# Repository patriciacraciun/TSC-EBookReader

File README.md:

# README 

## Descriere Generala

Acest proiect reprezinta un sistem integrat cu afisaj E-Paper, conectivitate wireless si mai multi senzori. Totul este construit in jurul microcontrollerului ESP32-C6, care ofera suport pentru WiFi 6 si Bluetooth LE.
Proiectul include atat partea de incarcare si monitorizare a bateriei, cat si stocare externa si masurare a conditiilor de mediu.

---

## Etapele de Implementare

- Am inceput cu realizarea schemei electrice, conectand toate componentele relevante la ESP32-C6.
- Apoi am trecut la layout-ul PCB-ului in 2D, unde am rutat liniile de date si alimentare.
- Am creat planuri de masa (GND plane) atat pe stratul superior, cat si inferior.
- Am folosit reguli custom pentru latimea traseelor de alimentare si distantele minime fata de alte semnale.
- Conectorii au fost pozitionati astfel incat sa fie usor accesibili (ex: Qwiic pentru senzori externi).
- Am adaugat pad-uri de test (TP) pentru debugging mai usor dupa asamblare.
- Am generat modele 3D pentru a verifica compatibilitatea mecanica si pozitionarea componentelor in carcasa.
---

## Diagrama Bloc

```text
         +------------+
         |  Baterie   |
         +------------+
               |
               v
       +----------------+
       |  Charging IC   |<-- USB-C
       +----------------+
               |
               v
       +----------------+
       |      LDO       | --> 3.3V
       +----------------+
               |
      +--------+--------+--------+--------+--------+
      v        v        v        v        v
   +------+ +--------+ +------+ +------+ +--------+
   | ESP  | |Display | | RTC  | | BME  | | Butoane|
   | -C6  | |(SPI)   | |(I2C) | |(I2C) | |(GPIO)  |
   +------+ +--------+ +------+ +------+ +--------+
               |
               v
           +---------+
           | Flash   |
           |  NOR    |
           | (SPI)   |
           +---------+
               |
               v
           +---------+
           | SD Card |
           |  (SPI)  |
           +---------+
```

---

## BOM (Bill Of Materials)

| Componenta                        | Link Cumparare                                                                                                   | Datasheet                                                                                          
|-----------------------------------|------------------------------------------------------------------------------------------------------------------|---------------------------------------------------------------------------------------------------
| 112A-TAAR-R03 ATTEND              | https://store.comet.srl.ro/Catalogue/Product/43497/                                                              | https://www.snapeda.com/parts/112A-TAAR-R03/Attend/datasheet/                                    
| BD5229G-TR                        | https://www.digikey.com/en/products/detail/rohm-semiconductor/BD5229G-TR/3663792                                 | https://fscdn.rohm.com/en/products/databook/datasheet/ic/power/voltage_detector/bd52xxg-e.pdf    
| ESP32 WROVER BME680 Sensor        | https://store.comet.srl.ro/Catalogue/Product/50164/                                                              | https://www.bosch-sensortec.com/media/boschsensortec/downloads/datasheets/bst-bme680-ds001.pdf   
| LED CHG_LED                       | https://ro.mouser.com/ProductDetail/Kingbright/KP-1608SURCK?qs=2JU0tDl2GZ3FuyEWfBV1%2Fg==                        | https://www.snapeda.com/parts/KP-1608SURCK/Kingbright/datasheet/                                 
| Condensator C0402                 | https://ro.mouser.com/c/passive-components/capacitors/ceramic-capacitors/?q=CC0402                               | https://componentsearchengine.com/Datasheets/2/CC0402MRX5R5BB106.pdf                             
| Condensator Tant                  | https://ro.mouser.com/ProductDetail/KYOCERA-AVX/TAJW107M010RNJ?qs=Wtp%252Bf%2FAeVqIH8v1VxV%252B1Rg%3D%3D         | https://ro.mouser.com/datasheet/2/40/TAJ-3165264.pdf                                             
| Q1 DMG2305UX-7                    | https://www.digikey.com/en/products/detail/diodes-incorporated/DMG2305UX-7/4340666                               | https://www.diodes.com/assets/Datasheets/DMG2305UX.pdf                                           
| RTC MODULE DS3231SN#              | https://www.snapeda.com/parts/DS3231SN%23/Analog+Devices/view-part/?ref=eda                                      | https://www.snapeda.com/parts/DS3231SN%23/Analog%20Devices/datasheet/                            
| ESP32 C6 WROOM-1-N8               | https://ro.mouser.com/ProductDetail/Espressif-Systems/ESP32-C6-WROOM-1-N8?qs=8Wlm6%252BaMh8ST02Gmwp74cw%3D%3D    | https://www.snapeda.com/parts/ESP32-C6-WROOM-1-N8/Espressif%20Systems/datasheet/                 
| FH34SRJ-24S-0.5SH(99)             | https://ro.mouser.com/ProductDetail/Hirose-Connector/FH34SRJ-24S-0.5SH99?qs=vcbW%252B4%252BSTIpKBl5ap9J8Fw%3D%3D | https://www.snapeda.com/parts/FH34SRJ-24S-0.5SH(99)/Hirose%20Connector/datasheet/                
| MAX 17048G+T10                    | https://www.snapeda.com/parts/MAX17048G+T10/Analog+Devices/view-part/?ref=eda                                    | https://www.snapeda.com/parts/MAX17048G+T10/Analog%20Devices/datasheet/                          
| MBR0530 Schottky Diode            | https://www.snapeda.com/parts/MBR0530/Onsemi/view-part/?ref=snap                                                 | https://www.snapeda.com/parts/MBR0530/ON%20Semiconductor/datasheet/                              
| MCP73831 Power Management         | https://www.snapeda.com/parts/MCP73831T-2ACI/OT/Microchip/datasheet/                                             | https://www.snapeda.com/parts/MCP73831T-2ACI/OT/Microchip/datasheet/                             
| PFMF.050.1                        | https://ro.mouser.com/ProductDetail/EPCOS-TDK/B72520T0350K062?qs=dEfas%2FXlABIszF52uu7vrg%3D%3D                  | https://www.tdk-electronics.tdk.com/inf/75/db/CTVS_14/Surge_protection_series.pdf                
| PGB1010603MR                      | https://www.snapeda.com/parts/PGB1010603MR/Littelfuse/view-part/?ref=eda                                         | https://www.snapeda.com/parts/PGB1010603MR/Littelfuse%20Inc./datasheet/                          
| QWIIC_RIGHT_ANGLE CONNECTOR       | https://ro.mouser.com/ProductDetail/SparkFun/PRT-14417?qs=wd5RIQLrsJhgdz%2FpmZ%2F3GQ==                           | https://ro.mouser.com/datasheet/2/813/Qwiic_Connector_Datasheet-1223982.pdf                      
| Rezistenta R0402                  | https://grabcad.com/library/resistor-0402-1)                                                                     | https://www.yageo.com/upload/media/product/products/datasheet/rchip/PYu-RC_Group_51_RoHS_L_12.pdf
| SD0805S020S1R0                    | https://ro.mouser.com/ProductDetail/KYOCERA-AVX/SD0805S020S1R0?qs=jCA%252BPfw4LHbpkAoSnwrdjw%3D%3D               | https://ro.mouser.com/datasheet/2/40/schottky-3165252.pdf                                        
| Si1308EDL-T1-GE3 MOSFET           | https://www.snapeda.com/parts/SI1308EDL-T1-GE3/Vishay+Siliconix/view-part/?welcome=home&ref=eda                  | https://www.snapeda.com/parts/SI1308EDL-T1-GE3/Vishay%20Siliconix/datasheet/                     
| USB4110-GF-A                      | https://ro.mouser.com/ProductDetail/GCT/USB4110-GF-A?qs=KUoIvG%2F9IlYiZvIXQjyJeA%3D%3D                           | https://ro.mouser.com/datasheet/2/837/GCT_USB4110_Product_Drawing___20k_cycles-3455479.pdf       
| USBLC6-2SC6Y                      | https://ro.mouser.com/ProductDetail/STMicroelectronics/USBLC6-2SC6Y?qs=gNDSiZmRJS%2FOgDexvXkdow%3D%3D            | https://ro.mouser.com/datasheet/2/389/usblc6_2sc6y-1852505.pdf                                   
| W25Q512JVEIQ                      | https://www.snapeda.com/parts/W25Q512JVEIQ/Winbond+Electronics/view-part/?ref=eda)                               | https://www.winbond.com/resource-files/W25Q512JV%20SPI%20RevB%2006252019%20KMS.pdf               
| XC6220A331MR-G                    | https://componentsearchengine.com/part-view/XC6220A331MR-G/Torex                                                 | https://product.torexsemi.com/system/files/series/xc6220.pdf                                     
| 744043680 BOBINA                  | https://ro.mouser.com/ProductDetail/Wurth-Elektronik/744043680?qs=PGXP4M47uW6VkZq%252BkzjrHA%3D%3D               | https://www.we-online.com/components/products/datasheet/744043680.pdf                            

---

## Functionalitate Hardware

Microcontrollerul ESP32-C6 gestioneaza toate functiile sistemului:

- **Display E-Paper**: conectat prin SPI. Este utilizat pentru afisajul principal.
- **BME688**: senzor de temperatura, umiditate, presiune si VOC, conectat prin I2C.
- **RTC DS3231**: modul de timp real, pentru pastrarea orei chiar si cand dispozitivul este oprit.
- **SD Card**: stocare externa, comunicare SPI.
- **Memorie NOR Flash**: pentru date si firmware, interfata SPI.
- **Charging controller (MCP73831)**: incarca bateria Li-Po prin USB-C.
- **Fuel gauge (MAX17048)**: monitorizeaza nivelul de incarcare al bateriei.
- **Qwiic Connector**: pentru senzori modulari, I2C.
- **Buton BOOT si RESET**: conectate la GPIO pentru programare si control.

---

## Alocarea Pinilor ESP32-C6

| Componenta                | Interfata | Pini ESP32-C6        | Observatii                          |
|--------------------------|-----------|----------------------|--------------------------------------|
| Display E-Paper          | SPI       | IO7, IO6, IO10, IO5, IO23, IO3 | MOSI, SCK, CS, DC, RST, BUSY       |
| BME688 + RTC             | I2C       | IO21 (SDA), IO22 (SCL) | Bus comun cu pull-up                |
| MAX17048 Battery Gauge   | I2C       | IO19 (SCL), IO20 (SDA)| Separat pentru alimentare baterie   |
| SD Card                  | SPI       | IO4 (CS) + MOSI/SCK/MISO| Partajate cu Flash/Display         |
| Flash NOR                | SPI       | IO12 (CS)             | Pe acelasi bus SPI                  |
| USB                      | USB       | IO13 (D+), IO12 (D-)  | Conexiune directa la USB-C          |
| Buton Reset              | GPIO      | EN                    | Reset hardware                      |
| Buton Boot               | GPIO      | IO9                   | Intrare manuala in modul bootloader |

---

## Alte Observatii

- Placa are pad-uri de test (TP) pentru debugging usor.
- Conectorul Qwiic permite extinderea cu alti senzori.
- Diodele ESD protejeaza liniile sensibile (USB, SPI, alimentare).
- Planurile de masa au fost implementate pe ambele straturi pentru stabilitate si protectie EMI.
- Rutarea a fost facuta manual, tinand cont de distantele minime si traseele de putere.
- PCB-ul este compact si poate fi reprodus usor in mai multe exemplare.
- Designul este compatibil cu carcase printate 3D.

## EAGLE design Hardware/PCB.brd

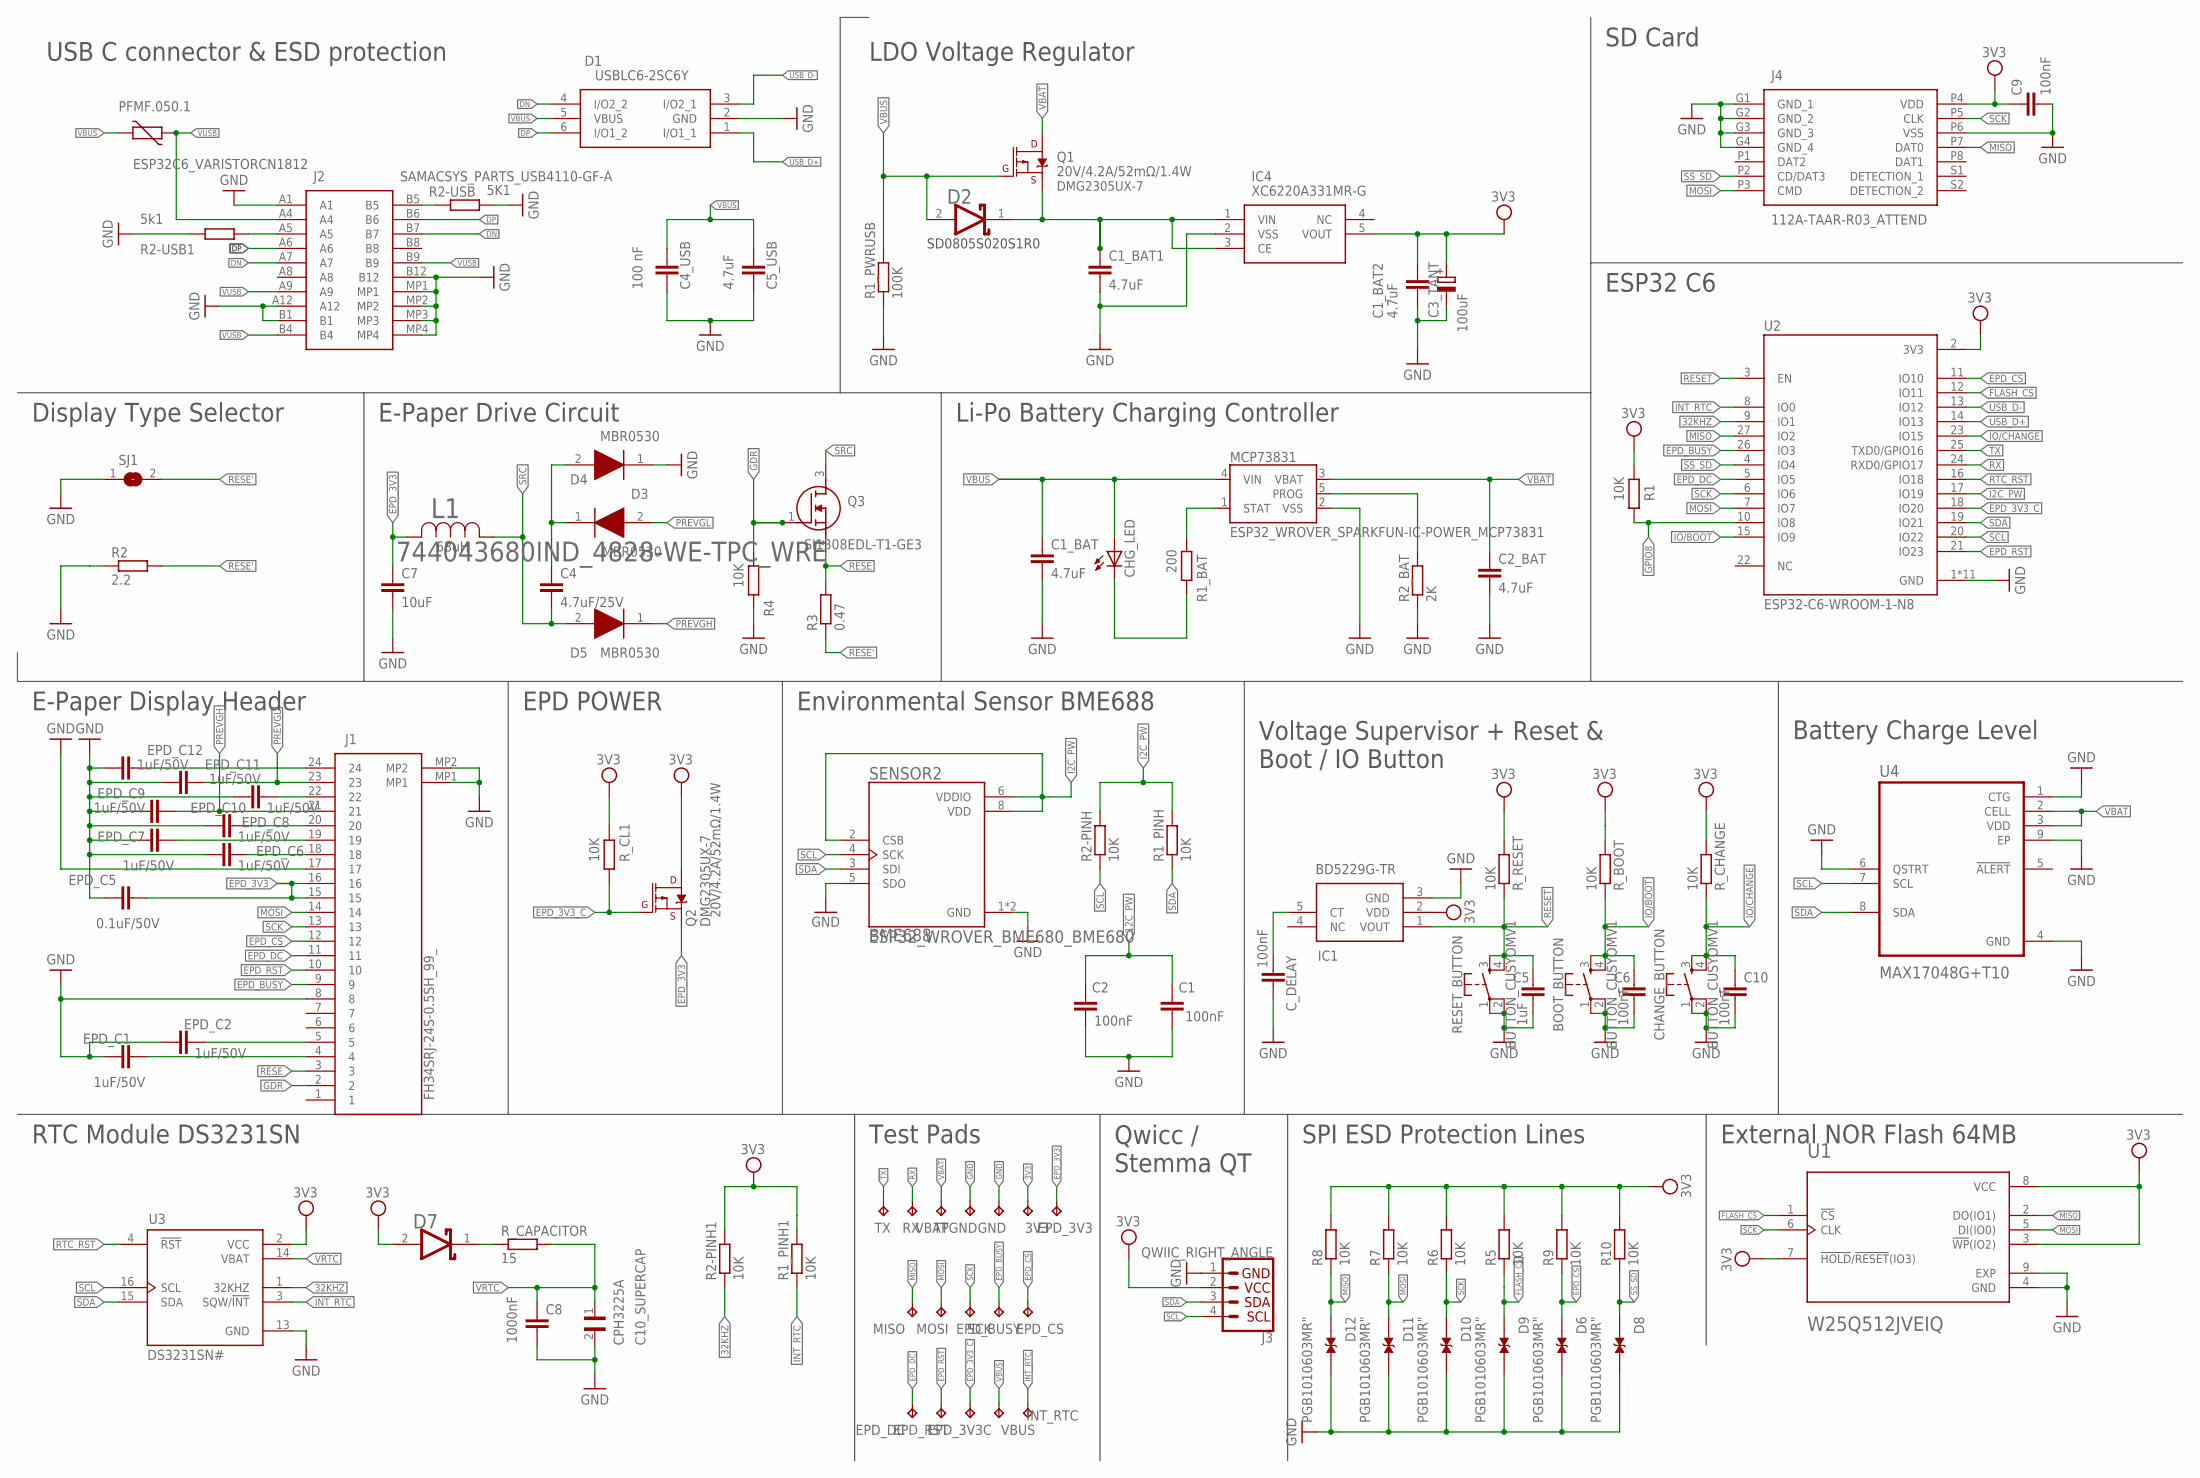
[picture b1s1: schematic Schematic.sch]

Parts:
3V3: TPTP20R; TP20R
BOOT_BUTTON: BUTTON_CUSYOMV1; MYBUTTON
C1, C2: 100nF; ESP32_WROVER_EAGLE-LTSPICE_C0402
C1_BAT, C1_BAT1, C1_BAT2, C2_BAT: 4.7uF; EAGLE-LTSPICE_C0402
C3_TANT: 100uF; RCL_CT3528
C4: 4.7uF/25V; EAGLE-LTSPICE_C0402
C4_USB: 100 nF; ESP32_WROVER_EAGLE-LTSPICE_C0402
C5: 1uF; EAGLE-LTSPICE_C0402
C5_USB: 4.7uF; ESP32_WROVER_EAGLE-LTSPICE_C0402
C6, C9, C10: 100nF; EAGLE-LTSPICE_C0402
C7: 10uF; EAGLE-LTSPICE_C0402
C8: 1000nF; EAGLE-LTSPICE_C0402
C10_SUPERCAP: CPH3225A; CAPCP3225X100N
CHANGE_BUTTON: BUTTON_CUSYOMV1; MYBUTTON
CHG_LED: ADAFRUIT_LEDCHIP-LED0603; ADAFRUIT_CHIP-LED0603
C_DELAY: 100nF; EAGLE-LTSPICE_C0402
D1: USBLC6-2SC6Y; SOT95P280X145-6N
D2, D7: ESP32_WROVER_AVX---SD0805S020S1R0_AVX_SD0805S020S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; ESP32_WROVER_AVX---SD0805S020S1R0_AVX_SD0805S020S1R0_0
D3, D4, D5: MBR0530; SOD3716X135N
D6, D8, D9, D10, D11, D12: PGB1010603MR"; DIOC1608X36N
EPD_3V3, EPD_3V3C: TPTP20R; TP20R
EPD_BUSY: TPTP20R; TP20R
EPD_C1, EPD_C2, EPD_C6, EPD_C7, EPD_C8, EPD_C9, EPD_C10, EPD_C11, EPD_C12: 1uF/50V; EAGLE-LTSPICE_C0402
EPD_C5: 0.1uF/50V; EAGLE-LTSPICE_C0402
EPD_CS: TPTP20R; TP20R
EPD_DC: TPTP20R; TP20R
EPD_RST: TPTP20R; TP20R
GND: TPTP20R; TP20R
IC1: BD5229G-TR; SOT95P280X125-5N
IC4: XC6220A331MR-G; SOT95P280X120-5N
INT_RTC: TPTP20R; TP20R
J1: FH34SRJ-24S-0.5SH_99_; FH34SRJ24S05SH99
J2: SAMACSYS_PARTS_USB4110-GF-A; SAMACSYS_PARTS_USB4110GFA
J3: QWIIC_RIGHT_ANGLE; JST04_1MM_RA
J4: 112A-TAAR-R03_ATTEND; 112ATAARR03ATTEND
L1: 744043680IND_4828-WE-TPC_WRE; IND_4828-WE-TPC_WRE
MCP73831: ESP32_WROVER_SPARKFUN-IC-POWER_MCP73831; ESP32_WROVER_SPARKFUN-IC-POWER_SOT23-5
MISO: TPTP20R; TP20R
MOSI: TPTP20R; TP20R
PFMF.050.1: ESP32C6_VARISTORCN1812; ESP32C6_VARISTOR_CT/CN1812
Q1, Q2: 20V/4.2A/52mΩ/1.4W; ESP32_WROVER_SPARKFUN-DISCRETESEMI_SOT23-3
Q3: SI1308EDL-T1-GE3; SOT65P210X110-3N
R1, R1_PINH, R1_PINH1, R2-PINH, R2-PINH1, R4, R5, R6, R7, R8, R9, R10: 10K; ESP32_WROVER_EAGLE-LTSPICE_R0402
R1_BAT: 200; ESP32_WROVER_EAGLE-LTSPICE_R0402
R1_PWRUSB: 100K; ESP32_WROVER_EAGLE-LTSPICE_R0402
R2: 2.2; ESP32_WROVER_EAGLE-LTSPICE_R0402
R2-USB: 5K1; ESP32_WROVER_EAGLE-LTSPICE_R0402
R2-USB1: 5k1; ESP32_WROVER_EAGLE-LTSPICE_R0402
R2_BAT: 2K; ESP32_WROVER_EAGLE-LTSPICE_R0402
R3: 0.47; ESP32_WROVER_EAGLE-LTSPICE_R0402
RESET_BUTTON: BUTTON_CUSYOMV1; MYBUTTON
RX: TPTP20R; TP20R
R_BOOT: 10K; ESP32_WROVER_EAGLE-LTSPICE_R0402
R_CAPACITOR: 15; ESP32_WROVER_EAGLE-LTSPICE_R0402
R_CHANGE: 10K; ESP32_WROVER_EAGLE-LTSPICE_R0402
R_CL1: 10K; ESP32_WROVER_EAGLE-LTSPICE_R0402
R_RESET: 10K; ESP32_WROVER_EAGLE-LTSPICE_R0402
SCK: TPTP20R; TP20R
SENSOR2: ESP32_WROVER_BME680_BME680; ESP32_WROVER_BME680_PSON80P300X300X100-8N
SJ1: SJ
TPGND: TPTP20R; TP20R
TX: TPTP20R; TP20R
U1: W25Q512JVEIQ; SON127P600X800X80-9N
U2: ESP32-C6-WROOM-1-N8; XCVR_ESP32-C6-WROOM-1-N8
U3: DS3231SN#; SOIC127P1032X265-16N
U4: MAX17048G+T10; SON50P200X200X80-9N
VBAT: TPTP20R; TP20R
VBUS: TPTP20R; TP20R

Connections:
3V3: 3V3.TP, C1_BAT2.1, C3_TANT.+, C9.1, D7.2 (ANODE), IC1.2 (VDD), IC4.5 (VOUT), J3.2, J4.P4 (VDD), Q2.3 (D), R1.2, R1_PINH1.2, R2-PINH1.2, R5.2, R6.2, R7.2, R8.2, R9.2, R10.2, R_BOOT.2, R_CHANGE.2, R_CL1.2, R_RESET.2, U1.3 (!WP!(IO2)), U1.7 (!HOLD!/!RESET!(IO3)), U1.8 (VCC), U2.2 (3V3), U3.2 (VCC)
12C_PW: C1.1, C2.1
32KHZ: R2-PINH1.1, U2.9 (IO1), U3.1 (32KHZ)
DMG2305UX-7: C1_BAT1.1, D2.1 (CATHODE), IC4.1 (VIN), IC4.3 (CE), Q1.2 (S)
DN: D1.4 (I/O2_2), J2.A7, J2.B7
DP: D1.6 (I/O1_2), J2.A6, J2.B6
EPD_3V3: C7.1, EPD_3V3.TP, EPD_C5.2, J1.15, J1.16, L1.2, Q2.2 (S)
EPD_3V3_C: EPD_3V3C.TP, Q2.1 (G), R_CL1.1, U2.18 (IO20)
EPD_BUSY: EPD_BUSY.TP, J1.9, U2.26 (IO3)
EPD_CS: D6.1, EPD_CS.TP, J1.12, R9.1, U2.11 (IO10)
EPD_DC: EPD_DC.TP, J1.11, U2.5 (IO5)
EPD_RST: EPD_RST.TP, J1.10, U2.21 (IO23)
FLASH_CS: D9.1, R5.1, U1.1 (!CS), U2.12 (IO11)
GDR: J1.2, Q3.1 (G), R4.2
GND: BOOT_BUTTON.1, BOOT_BUTTON.2, C1.2, C1_BAT.2, C1_BAT1.2, C1_BAT2.2, C2.2, C2_BAT.2, C3_TANT.-, C4_USB.2, C5.2, C5_USB.2, C6.2, C7.2, C8.2, C9.2, C10.2, C10_SUPERCAP.2, CHANGE_BUTTON.1, CHANGE_BUTTON.2, C_DELAY.2, D1.2 (GND), D4.1 (K), D6.2, D8.2, D9.2, D10.2, D11.2, D12.2, EPD_C1.1, EPD_C2.1, EPD_C5.1, EPD_C6.1, EPD_C7.1, EPD_C8.1, EPD_C9.1, EPD_C10.1, EPD_C11.1, EPD_C12.1, GND.TP, IC1.3 (GND), IC4.2 (VSS), J1.8, J1.17, J1.MP1, J1.MP2, J2.A1, J2.A12, J2.B1, J2.B12, J2.MP1, J2.MP2, J2.MP3, J2.MP4, J3.1, J4.G1 (GND_1), J4.G2 (GND_2), J4.G3 (GND_3), J4.G4 (GND_4), J4.P6 (VSS), MCP73831.2 (VSS), R1_PWRUSB.1, R2.1, R2-USB.2, R2-USB1.1, R2_BAT.1, R4.1, RESET_BUTTON.1, RESET_BUTTON.2, SENSOR2.1 (GND), SENSOR2.5 (SDO), SENSOR2.7 (GND), SJ1.1, TPGND.TP, U1.4 (GND), U1.9 (EXP), U2.1 (GND), U2.28 (GND), U2.29_1 (GND), U2.29_2 (GND), U2.29_3 (GND), U2.29_4 (GND), U2.29_5 (GND), U2.29_6 (GND), U2.29_7 (GND), U2.29_8 (GND), U2.29_9 (GND), U3.13 (GND), U4.1 (CTG), U4.4 (GND), U4.6 (QSTRT), U4.9 (EP)
GPIO8: R1.1, U2.10 (IO8)
I2C_PW: R1_PINH.2, R2-PINH.2, SENSOR2.2 (CSB), SENSOR2.6 (VDDIO), SENSOR2.8 (VDD), U2.17 (IO19)
INT_RTC: INT_RTC.TP, R1_PINH1.1, U2.8 (IO0), U3.3 (SQW/!INT)
IO/BOOT: BOOT_BUTTON.3, BOOT_BUTTON.4, C6.1, R_BOOT.1, U2.15 (IO9)
IO/CHANGE: C10.1, CHANGE_BUTTON.3, CHANGE_BUTTON.4, R_CHANGE.1, U2.23 (IO15)
MISO: D12.1, J4.P7 (DAT0), MISO.TP, R8.1, U1.2 (DO(IO1)), U2.27 (IO2)
MOSI: D11.1, J1.14, J4.P3 (CMD), MOSI.TP, R7.1, U1.5 (DI(IO0)), U2.7 (IO7)
unnamed: J2.B5, R2-USB.1
unnamed: EPD_C12.2, J1.24
unnamed: J2.A5, R2-USB1.2
unnamed: C4.1, D3.1 (K), D4.2 (A)
unnamed: CHG_LED.C, R1_BAT.1
unnamed: MCP73831.1 (STAT), R1_BAT.2
unnamed: MCP73831.5 (PROG), R2_BAT.2
unnamed: C_DELAY.1, IC1.5 (CT)
unnamed: EPD_C10.2, J1.22
unnamed: EPD_C8.2, J1.20
unnamed: EPD_C7.2, J1.19
unnamed: EPD_C6.2, J1.18
unnamed: D7.1 (CATHODE), R_CAPACITOR.1
unnamed: EPD_C2.2, J1.5
unnamed: EPD_C1.2, J1.4
PREVGH: D5.1 (K), EPD_C9.2, J1.21
PREVGL: D3.2 (A), EPD_C11.2, J1.23
RESE: J1.3, Q3.2 (S), R3.2
RESE': R2.2, R3.1, SJ1.2
RESET: C5.1, IC1.1 (VOUT), RESET_BUTTON.3, RESET_BUTTON.4, R_RESET.1, U2.3 (EN)
RTC_RST: U2.16 (IO18), U3.4 (!RST)
RX: RX.TP, U2.24 (RXD0/GPIO17)
SCK: D10.1, J1.13, J4.P5 (CLK), R6.1, SCK.TP, U1.6 (CLK), U2.6 (IO6)
SCL: J3.4, R2-PINH.1, SENSOR2.4 (SCK), U2.20 (IO22), U3.16 (SCL), U4.7 (SCL)
SDA: J3.3, R1_PINH.1, SENSOR2.3 (SDI), U2.19 (IO21), U3.15 (SDA), U4.8 (SDA)
SRC: C4.2, D5.2 (A), L1.1, Q3.3 (D)
SS_SD: D8.1, J4.P2 (CD/DAT3), R10.1, U2.4 (IO4)
TX: TX.TP, U2.25 (TXD0/GPIO16)
USB_D+: D1.1 (I/O1_1), U2.14 (IO13)
USB_D-: D1.3 (I/O2_1), U2.13 (IO12)
VBAT: C2_BAT.1, MCP73831.3 (VBAT), Q1.3 (D), U4.2 (CELL), U4.3 (VDD), VBAT.TP
VBUS: C1_BAT.1, C4_USB.1, C5_USB.1, CHG_LED.A, D1.5 (VBUS), D2.2 (ANODE), MCP73831.4 (VIN), PFMF.050.1.2, Q1.1 (G), R1_PWRUSB.2, VBUS.TP
VRTC: C8.1, C10_SUPERCAP.1, R_CAPACITOR.2, U3.14 (VBAT)
VUSB: J2.A4, J2.A9, J2.B4, J2.B9, PFMF.050.1.1

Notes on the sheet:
USB C connector & ESD protection
LDO Voltage Regulator
SD0805S020S1R0
SD Card
Display Type Selector
E-Paper Drive Circuit
Li-Po Battery Charging Controller
ESP32 C6
E-Paper Display Header
EPD POWER
DMG2305UX-7
Environmental Sensor BME688
BME688
Voltage Supervisor + Reset & Boot / IO Button
Battery Charge Level
RTC Module DS3231SN
Test Pads
Qwicc / Stemma QT
SPI ESD Protection Lines
External NOR Flash 64MB

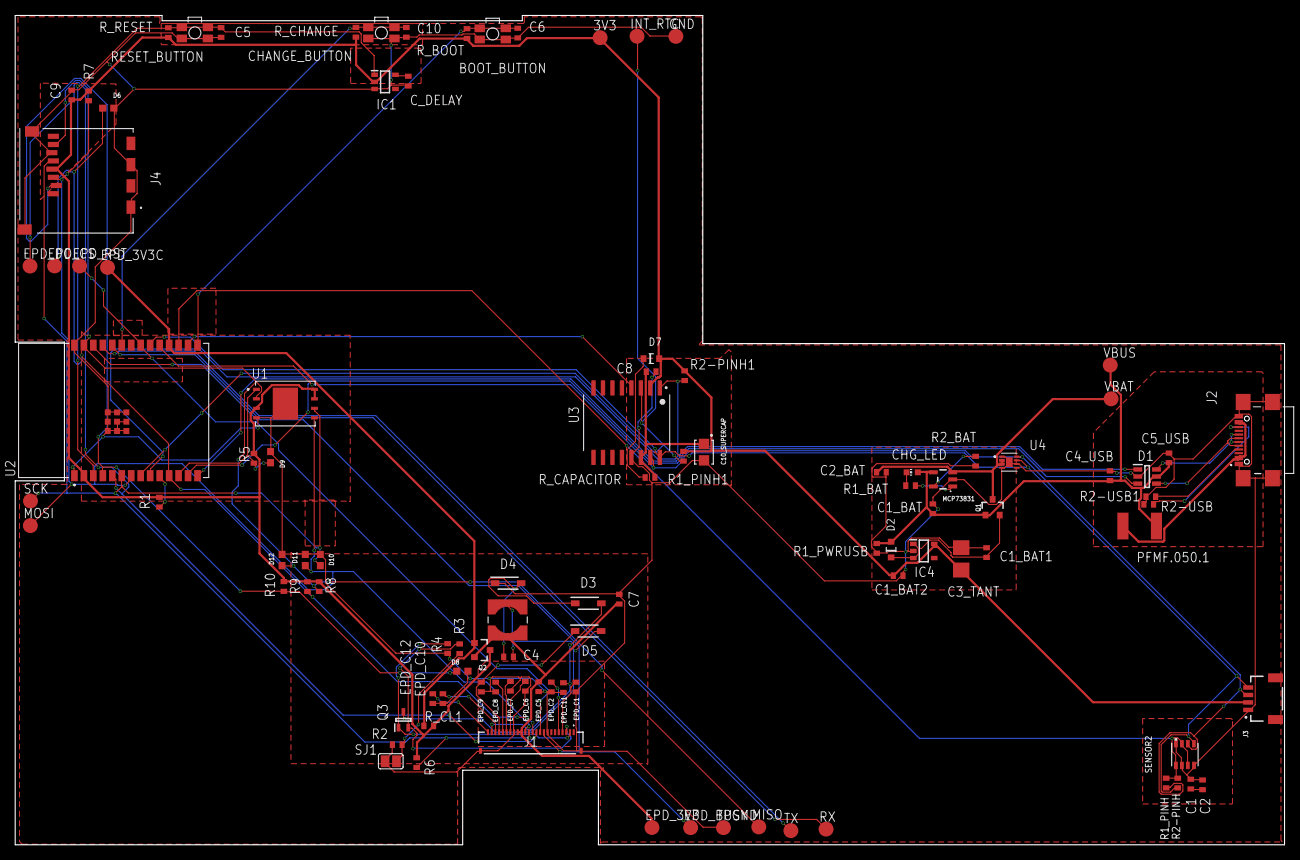
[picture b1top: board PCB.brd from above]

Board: 2 copper layers, 170.2 x 111.2 mm, 103 parts (0 on the bottom side), 56 nets.

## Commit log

2025-04-06 Create LICENSE

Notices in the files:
parts and their libraries:
COPYRIGHT: Copyright (C) 2024 Ultra Librarian. All rights reserved.
